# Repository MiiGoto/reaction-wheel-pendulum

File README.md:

# reaction-wheel-pendulum

最新方針（2026-10-08）: [1軸を保持して3軸へ発展する案B](docs/design_direction.md)を暫定第一候補にしました。指定X機体の同一性は未確認。GB54直結の自力起き上がりは仮定付き角運動量screeningで不適合。新しい[Inventor配置概念/STEP](mechanical/cubli_concept/README.md)と固定支点simulationを追加しましたが、製作可能な機構・実機性能・起き上がりは未完成です。[検証計画](docs/validation_plan.md)を参照してください。既存1軸native設計と未コミット変更は元checkoutに保持。

以下は既存1軸PCBの基準。機構・motor・driverの採用確定を意味しません。

1自由度リアクションホイール型倒立振子を製作し、制御モデルと実機の対応を検証する開発プロジェクトです。回路、STM32ファームウェア、シミュレーション、機構、試験記録を一つのGit repositoryで管理します。

## Project overview / System concept

BLDCでホイールを加減速し、その反作用で振子の姿勢を制御します。IMU、振子角度、ホイール角度・速度を取得し、PCでログを収集します。寸法目安は振子長約220 mm、ホイール径約130 mm、ホイール質量候補約90 gです。重心・慣性・最大速度・必要トルクは未決です。

## Hardware

制御基板MCUはSTM32G431RBT6（LQFP64、128 KB Flash / 32 KB RAM）を採用。NucleoとB-G431B-ESC1を評価候補とし、初期試作では外部ESCを優先します。Task 2では安定化5 V入力、AP2112K-3.3 LDO、MCU基本回路とSWDを実装。Task 3ではTCAN3413DR CAN FD、LSM6DSLTR SPI、外付け3.3 V ABI Encoder、外部ESC PWM/ENABLE/FAULT、UART接続を追加。Encoder/ESCの型番、最高RPM、モータ電源は未決です。

KiCad 10.0.6で `hardware/kicad/reaction_wheel_controller.kicad_pro` を開きます。rootは概念ブロックの概要、階層sheetはMCU/電源/SWD、CAN/IMU、Encoder/ESC、UARTに分割した実回路です。Task 4で90×70 mm・4層・4点M3固定穴の暫定PCB配置を追加しました。Task 5で全ネットの配線とprototype範囲のPCBレビューを完了しました。DRC Error0／Warning0／未配線0。製造承認・実機検証は未実施です。ERCの合格は実回路の正しさを意味しません。

## Firmware

`firmware/stm32/` は評価方針と要件を保管します。ターゲット・ESC通信方式の決定後にCubeMX/CubeIDEプロジェクトを作成します。まだ実行可能なファームウェアはありません。

## Simulation

`simulation/` はモデル仕様の初期整理です。実測または根拠のあるパラメータを登録した後、非線形モデル、線形化、PID、状態フィードバック、LQR、swing-up、推定、同定、sim2realへ進みます。現時点で制御性能は検証されていません。

## Repository structure

```text
hardware/kicad/   KiCad project, concept overview, MCU/power/SWD and interface schematics
firmware/stm32/   Firmware scope and future STM32 project
simulation/      Model and parameter requirements
mechanical/      Geometry, inertia and fixture requirements
docs/            Architecture, pin needs, power, bring-up, evidence
test/            Verification plan
```

最初に [PROJECT_CONTEXT.md](PROJECT_CONTEXT.md)、[requirements.md](requirements.md)、[AGENTS.md](AGENTS.md) を読んでください。環境調査は [docs/environment.md](docs/environment.md)、資料確認状態は [docs/sources.md](docs/sources.md) に記録します。

## Current status

Task5の配線・prototype範囲のレビューを完了しました。KiCad10.0.6のDRC Error0／Warning0／未配線0／回路図等価性問題0、ERC Error0／意図的Warning1。90×70mm・4層、548配線segment・155via、全部品配置と電気pin assignmentを保持しています。

[最新routing review](docs/task5_routing_review.md)、[current checkpoint](docs/task5_routing_checkpoint.md)、[検証記録](docs/validation.md)。実際のESC／Encoder、最終BOM・製造stackup・実装・安全性・熱・EMIの確認は未完了です。製造データ・注文・firmware・通電試験・Task6は未実施です。

## Roadmap

1. 機構パラメータ、電源、BLDC、双方向トルクを扱えるESCと制御指令仕様を確定。
2. 評価ボードでセンサ取得、安全停止、PC logging、モータ単体評価。
3. 必要I/Oを確定し、MCU型番・packageと物理ピン番号を公式資料・CubeMXで照合。
4. 電源・MCU・デバッグの回路を段階的に作成し、毎回ERCを実行。
5. CAN・センサ・ESC接続を追加し、要求追跡とレビューを実施。
6. シミュレーションと同定により制御を検証し、安全治具で実機評価。
7. 回路承認後にPCB設計・DRC・製造レビューへ進む。

## Publication and license

公開ファイルは本プロジェクト用の文書・設計です。回路図内のKiCad標準symbolは[ライブラリの設計成果物例外](https://www.kicad.org/libraries/license/)を確認済みです。ベンダーのPDF、SDK、HAL、独立した第三者ライブラリ集、ツールの実行ファイルは含めません。プロジェクトのライセンス選択はTBDです。公開されていること自体は第三者コードの利用許諾を意味しません。

## Detailed Cubli Rev A status (2026-10-08)

Detailed fabrication CAD has **not** been completed. The three-axis clearance
study is preserved. A new motor/brake/contact gate identifies insufficient GB54
momentum and an unsafe direct cantilever brake-loaded motor shaft. Three named
motor alternatives and three size options are compared in
[the Rev A gate report](docs/cubli_reva_design_gate.md). No new manufacturing
files or physical actions are released. Requested detailed CAD remains blocked
pending a qualified actuator/brake/support/power module.

## Current one-wheel native CAD milestone

Inventor2026.2で36部品・104拘束の1輪モジュールを作成、保存後に再読込しました。7姿勢のネイティブ干渉検査は0件。STEP37件／STL3件／保留付き図面14件を生成。ブレーキアクチュエータ・継手・保持公差・強度と3軸起き上がりは未検証です。製造承認済みではありません。詳細は[検証報告](docs/one_wheel_module_review.md)と[モジュール成果](mechanical/cubli_reva/one_wheel_module/README.md)を参照してください。

Rev B: actual lightened Inventor one-wheel module and orthogonal three-axis packing study.
See [review](docs/cubli_revb_review.md) and [manufacturing holds](docs/manufacturing_holds.md).
Self-righting, high-speed safety and fabrication remain unqualified. Native CAD is local; own STEP/PDF/scripts published.

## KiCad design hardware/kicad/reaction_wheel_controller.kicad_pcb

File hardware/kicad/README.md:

# reaction_wheel_controller

KiCad10.0.6でreaction_wheel_controller.kicad_proを開く。rootは概念概要、階層sheetはMCU/電源/SWD、CAN/IMU、Encoder/ESC、UARTの実回路。Task5でreaction_wheel_controller.kicad_pcbの全ネット配線を完了。90x70mm、4層、86footprints、548segments、155via、R0.5。

NativeDRC0Errors/0Warnings/0unrouted/0parity、ERC0Errors/1intentionalSDX/GNDWarning。主要設計ファイルとproject-local symbol table、custom design rulesを追跡。outputs/はlocal report・preview・checkpoint用でignored。VendorPDF/tools/SDK、Gerber/drill/PnPは公開せず、製造出力自体未実施。

DRC合格は製造承認・実機適合ではない。ExactBOM/stackup/assembly/encoder/ESC/mechanical/safety/thermal/EMIは未検証。[routing review](../../docs/task5_routing_review.md)、[validation](../../docs/validation.md)、[bring-up](../../docs/bringup.md)参照。未使用/予約MCUpinは意図的NC、firmware未実装。

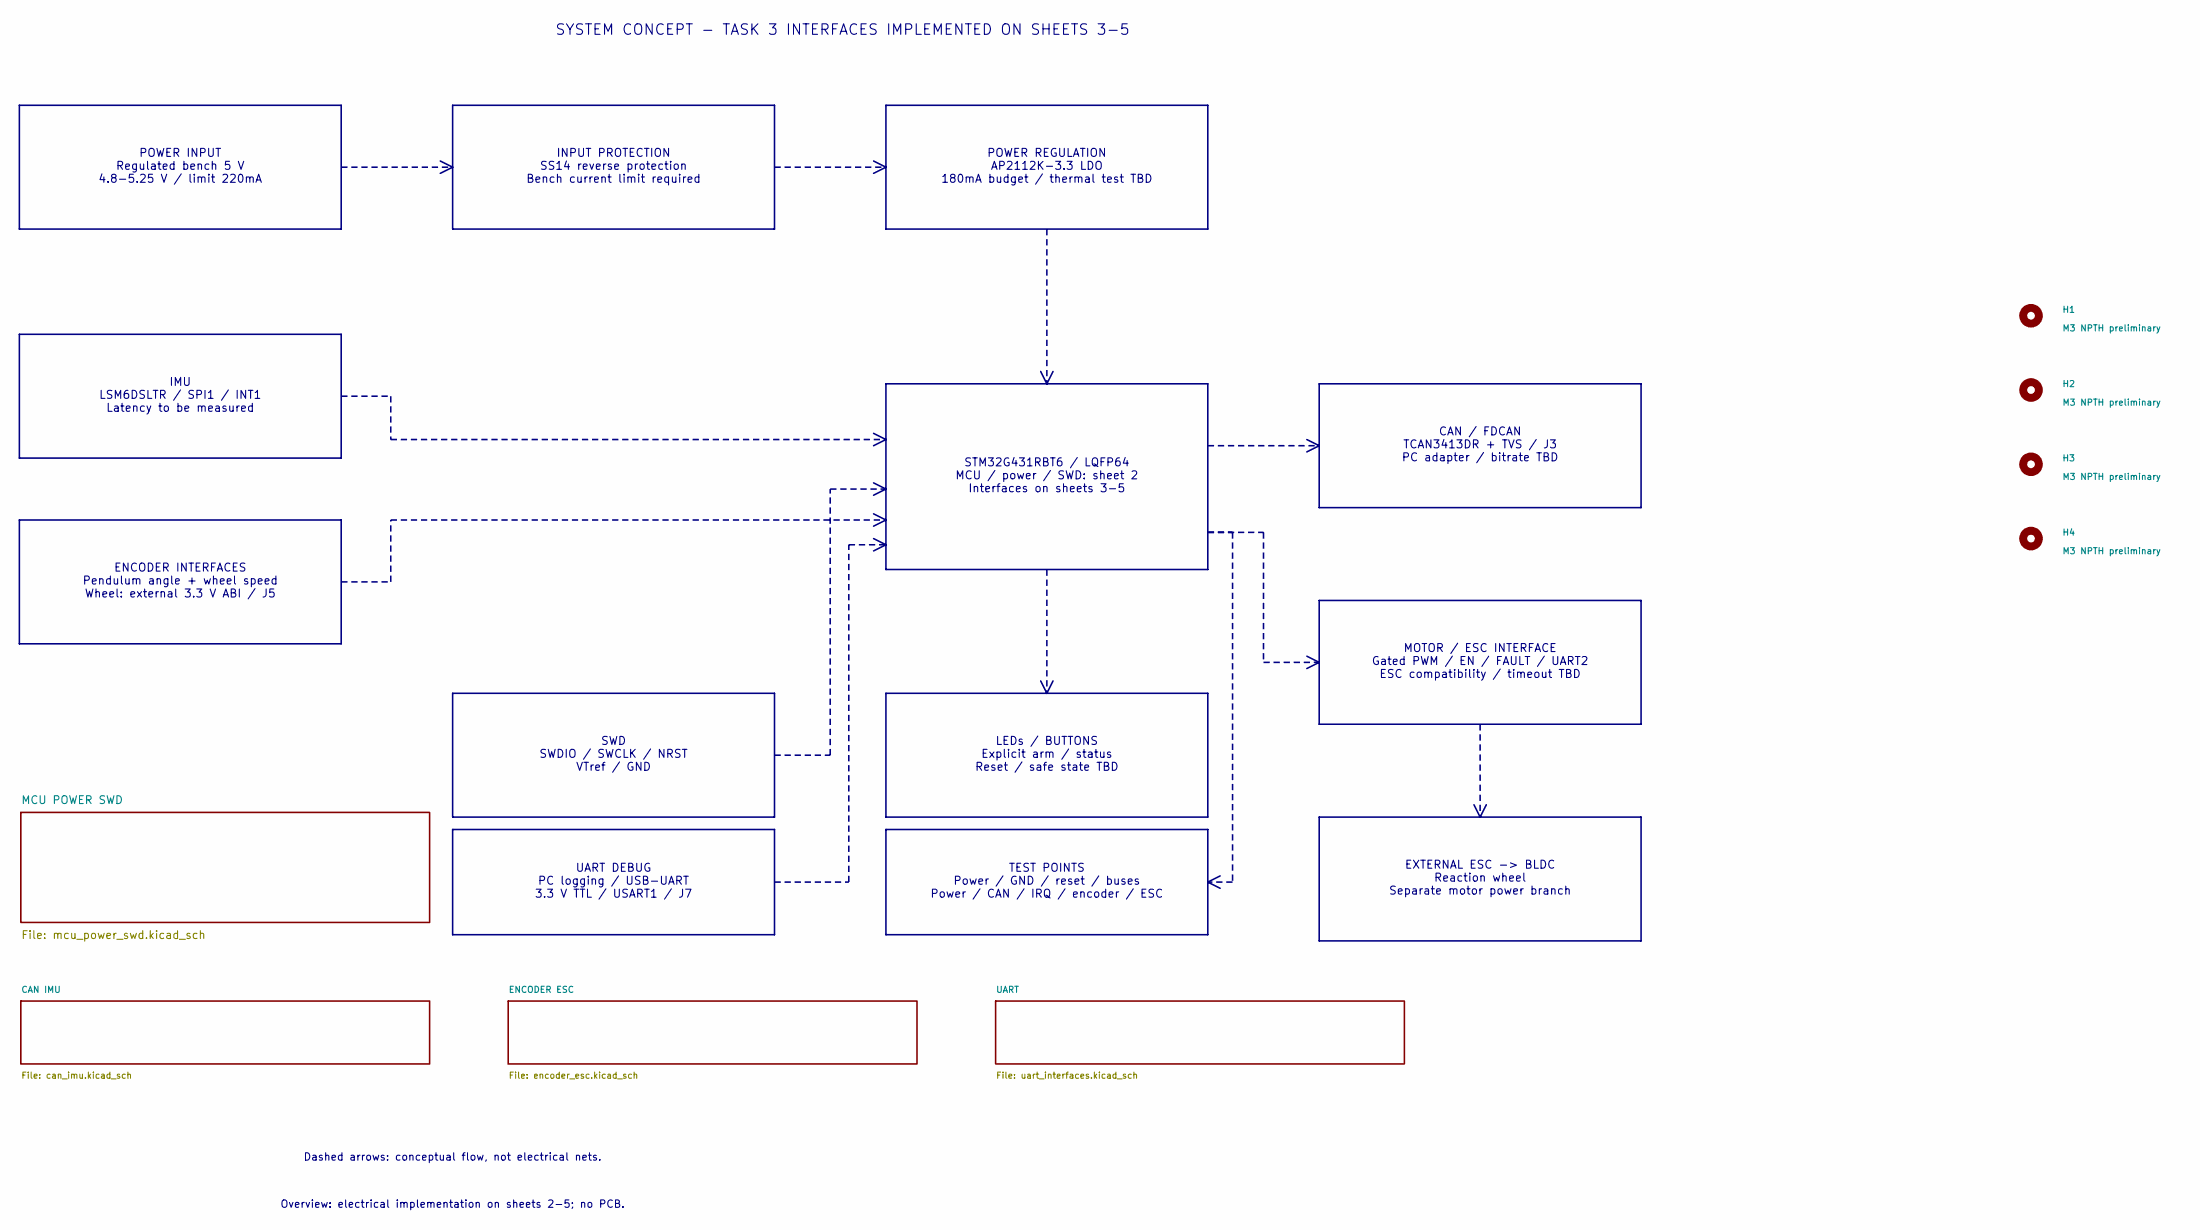
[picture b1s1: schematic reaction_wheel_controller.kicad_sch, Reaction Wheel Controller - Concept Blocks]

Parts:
H1, H2, H3, H4: M3 NPTH preliminary; MountingHole_3.2mm_M3

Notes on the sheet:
SYSTEM CONCEPT - TASK 3 INTERFACES IMPLEMENTED ON SHEETS 3-5
POWER INPUT Regulated bench 5 V 4.8-5.25 V / limit 220mA
INPUT PROTECTION SS14 reverse protection Bench current limit required
POWER REGULATION AP2112K-3.3 LDO 180mA budget / thermal test TBD
STM32G431RBT6 / LQFP64 MCU / power / SWD: sheet 2 Interfaces on sheets 3-5
IMU LSM6DSLTR / SPI1 / INT1 Latency to be measured
ENCODER INTERFACES Pendulum angle + wheel speed Wheel: external 3.3 V ABI / J5
CAN / FDCAN TCAN3413DR + TVS / J3 PC adapter / bitrate TBD
MOTOR / ESC INTERFACE Gated PWM / EN / FAULT / UART2 ESC compatibility / timeout TBD
EXTERNAL ESC -> BLDC Reaction wheel Separate motor power branch
SWD SWDIO / SWCLK / NRST VTref / GND
UART DEBUG PC logging / USB-UART 3.3 V TTL / USART1 / J7
LEDs / BUTTONS Explicit arm / status Reset / safe state TBD
TEST POINTS Power / GND / reset / buses Power / CAN / IRQ / encoder / ESC
Dashed arrows: conceptual flow, not electrical nets.
Overview: electrical implementation on sheets 2-5; no PCB.

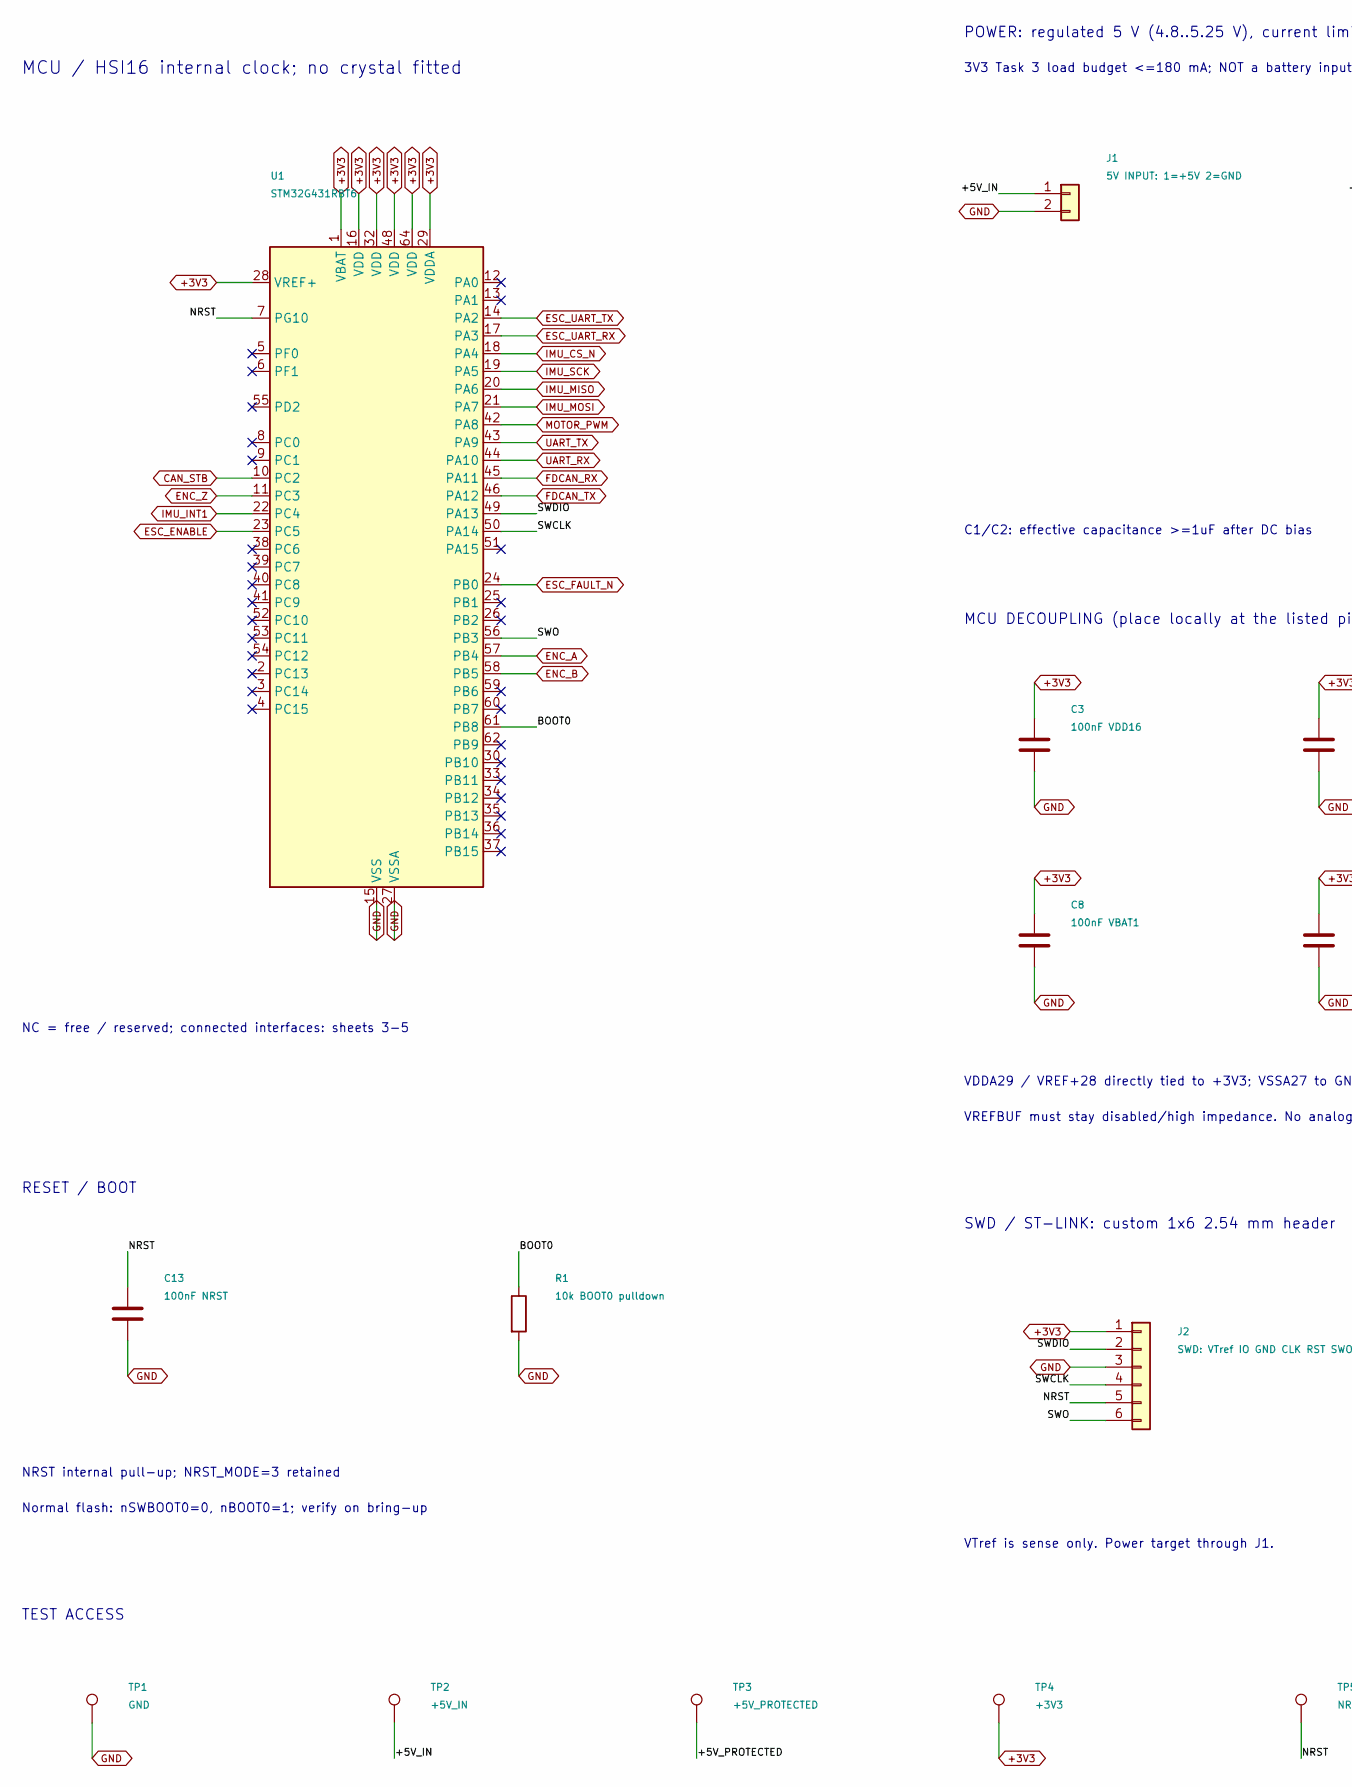
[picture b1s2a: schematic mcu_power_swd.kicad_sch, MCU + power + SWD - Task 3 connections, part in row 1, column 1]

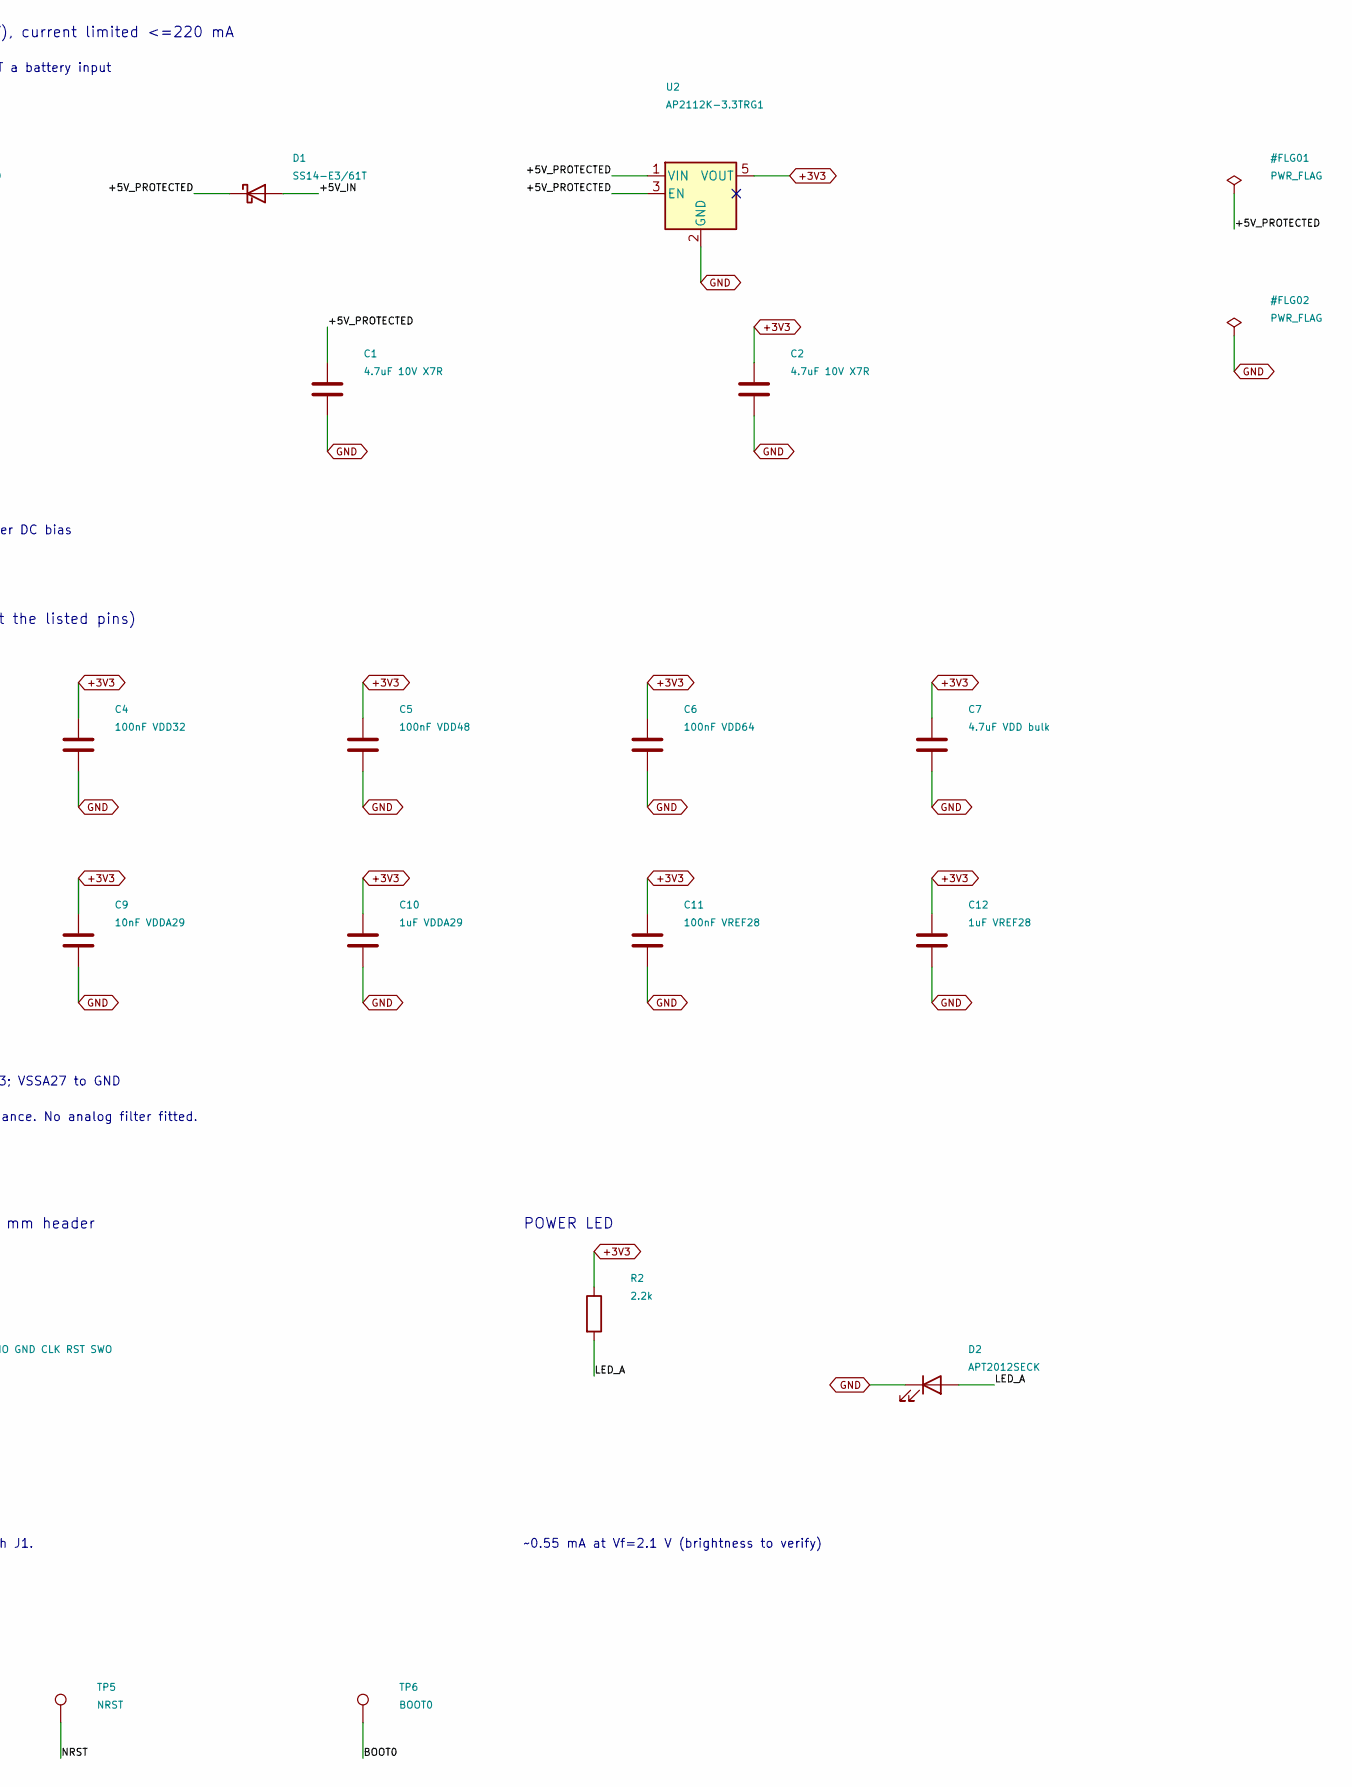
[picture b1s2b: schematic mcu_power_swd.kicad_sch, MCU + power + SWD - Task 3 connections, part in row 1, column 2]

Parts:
C1, C2: 4.7uF 10V X7R; C_0805_2012Metric
C3: 100nF VDD16; C_0805_2012Metric
C4: 100nF VDD32; C_0805_2012Metric
C5: 100nF VDD48; C_0805_2012Metric
C6: 100nF VDD64; C_0805_2012Metric
C7: 4.7uF VDD bulk; C_0805_2012Metric
C8: 100nF VBAT1; C_0805_2012Metric
C9: 10nF VDDA29; C_0805_2012Metric
C10: 1uF VDDA29; C_0805_2012Metric
C11: 100nF VREF28; C_0805_2012Metric
C12: 1uF VREF28; C_0805_2012Metric
C13: 100nF NRST; C_0805_2012Metric
D1: SS14-E3/61T; D_SMA
D2: APT2012SECK; LED_0805_2012Metric
J1: 5V INPUT: 1=+5V 2=GND; PinHeader_1x02_P2.54mm_Vertical
J2: SWD: VTref IO GND CLK RST SWO; PinHeader_1x06_P2.54mm_Vertical
R1: 10k BOOT0 pulldown; R_0805_2012Metric
R2: 2.2k; R_0805_2012Metric
TP1: GND; TestPoint_Pad_D1.5mm
TP2: +5V_IN; TestPoint_Pad_D1.5mm
TP3: +5V_PROTECTED; TestPoint_Pad_D1.5mm
TP4: +3V3; TestPoint_Pad_D1.5mm
TP5: NRST; TestPoint_Pad_D1.5mm
TP6: BOOT0; TestPoint_Pad_D1.5mm
U1: STM32G431RBT6; LQFP-64_10x10mm_P0.5mm
U2: AP2112K-3.3TRG1; SOT-23-5

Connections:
+3V3: C2.1, C3.1, C4.1, C5.1, C6.1, C7.1, C8.1, C9.1, C10.1, C11.1, C12.1, J2.1, R2.1, TP4.1, U1.1 (VBAT), U1.16 (VDD), U1.28 (VREF+), U1.29 (VDDA), U1.32 (VDD), U1.48 (VDD), U1.64 (VDD), U2.5 (VOUT); also elsewhere on the board
/MCU POWER SWD/+5V_IN: D1.2 (A), J1.1, TP2.1
/MCU POWER SWD/+5V_PROTECTED: C1.1, D1.1 (K), TP3.1, U2.1 (VIN), U2.3 (EN)
/MCU POWER SWD/BOOT0: R1.1, TP6.1, U1.61 (PB8)
/MCU POWER SWD/LED_A: D2.2 (A), R2.2
/MCU POWER SWD/NRST: C13.1, J2.5, TP5.1, U1.7 (PG10)
/MCU POWER SWD/SWCLK: J2.4, U1.50 (PA14)
/MCU POWER SWD/SWDIO: J2.2, U1.49 (PA13)
/MCU POWER SWD/SWO: J2.6, U1.56 (PB3)
CAN_STB: U1.10 (PC2); also elsewhere on the board
ENC_A: U1.57 (PB4); also elsewhere on the board
ENC_B: U1.58 (PB5); also elsewhere on the board
ENC_Z: U1.11 (PC3); also elsewhere on the board
ESC_ENABLE: U1.23 (PC5); also elsewhere on the board
ESC_FAULT_N: U1.24 (PB0); also elsewhere on the board
ESC_UART_RX: U1.17 (PA3); also elsewhere on the board
ESC_UART_TX: U1.14 (PA2); also elsewhere on the board
FDCAN_RX: U1.45 (PA11); also elsewhere on the board
FDCAN_TX: U1.46 (PA12); also elsewhere on the board
GND: C1.2, C2.2, C3.2, C4.2, C5.2, C6.2, C7.2, C8.2, C9.2, C10.2, C11.2, C12.2, C13.2, D2.1 (K), J1.2, J2.3, R1.2, TP1.1, U1.15 (VSS), U1.27 (VSSA), U1.31 (VSS), U1.47 (VSS), U1.63 (VSS), U2.2 (GND); also elsewhere on the board
IMU_CS_N: U1.18 (PA4); also elsewhere on the board
IMU_INT1: U1.22 (PC4); also elsewhere on the board
IMU_MISO: U1.20 (PA6); also elsewhere on the board
IMU_MOSI: U1.21 (PA7); also elsewhere on the board
IMU_SCK: U1.19 (PA5); also elsewhere on the board
MOTOR_PWM: U1.42 (PA8); also elsewhere on the board
UART_RX: U1.44 (PA10); also elsewhere on the board
UART_TX: U1.43 (PA9); also elsewhere on the board

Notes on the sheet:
MCU / HSI16 internal clock; no crystal fitted
NC = free / reserved; connected interfaces: sheets 3-5
POWER: regulated 5 V (4.8..5.25 V), current limited <=220 mA
3V3 Task 3 load budget <=180 mA; NOT a battery input
C1/C2: effective capacitance >=1uF after DC bias
MCU DECOUPLING (place locally at the listed pins)
VDDA29 / VREF+28 directly tied to +3V3; VSSA27 to GND
VREFBUF must stay disabled/high impedance. No analog filter fitted.
RESET / BOOT
NRST internal pull-up; NRST_MODE=3 retained
Normal flash: nSWBOOT0=0, nBOOT0=1; verify on bring-up
SWD / ST-LINK: custom 1x6 2.54 mm header
VTref is sense only. Power target through J1.
POWER LED
~0.55 mA at Vf=2.1 V (brightness to verify)
TEST ACCESS

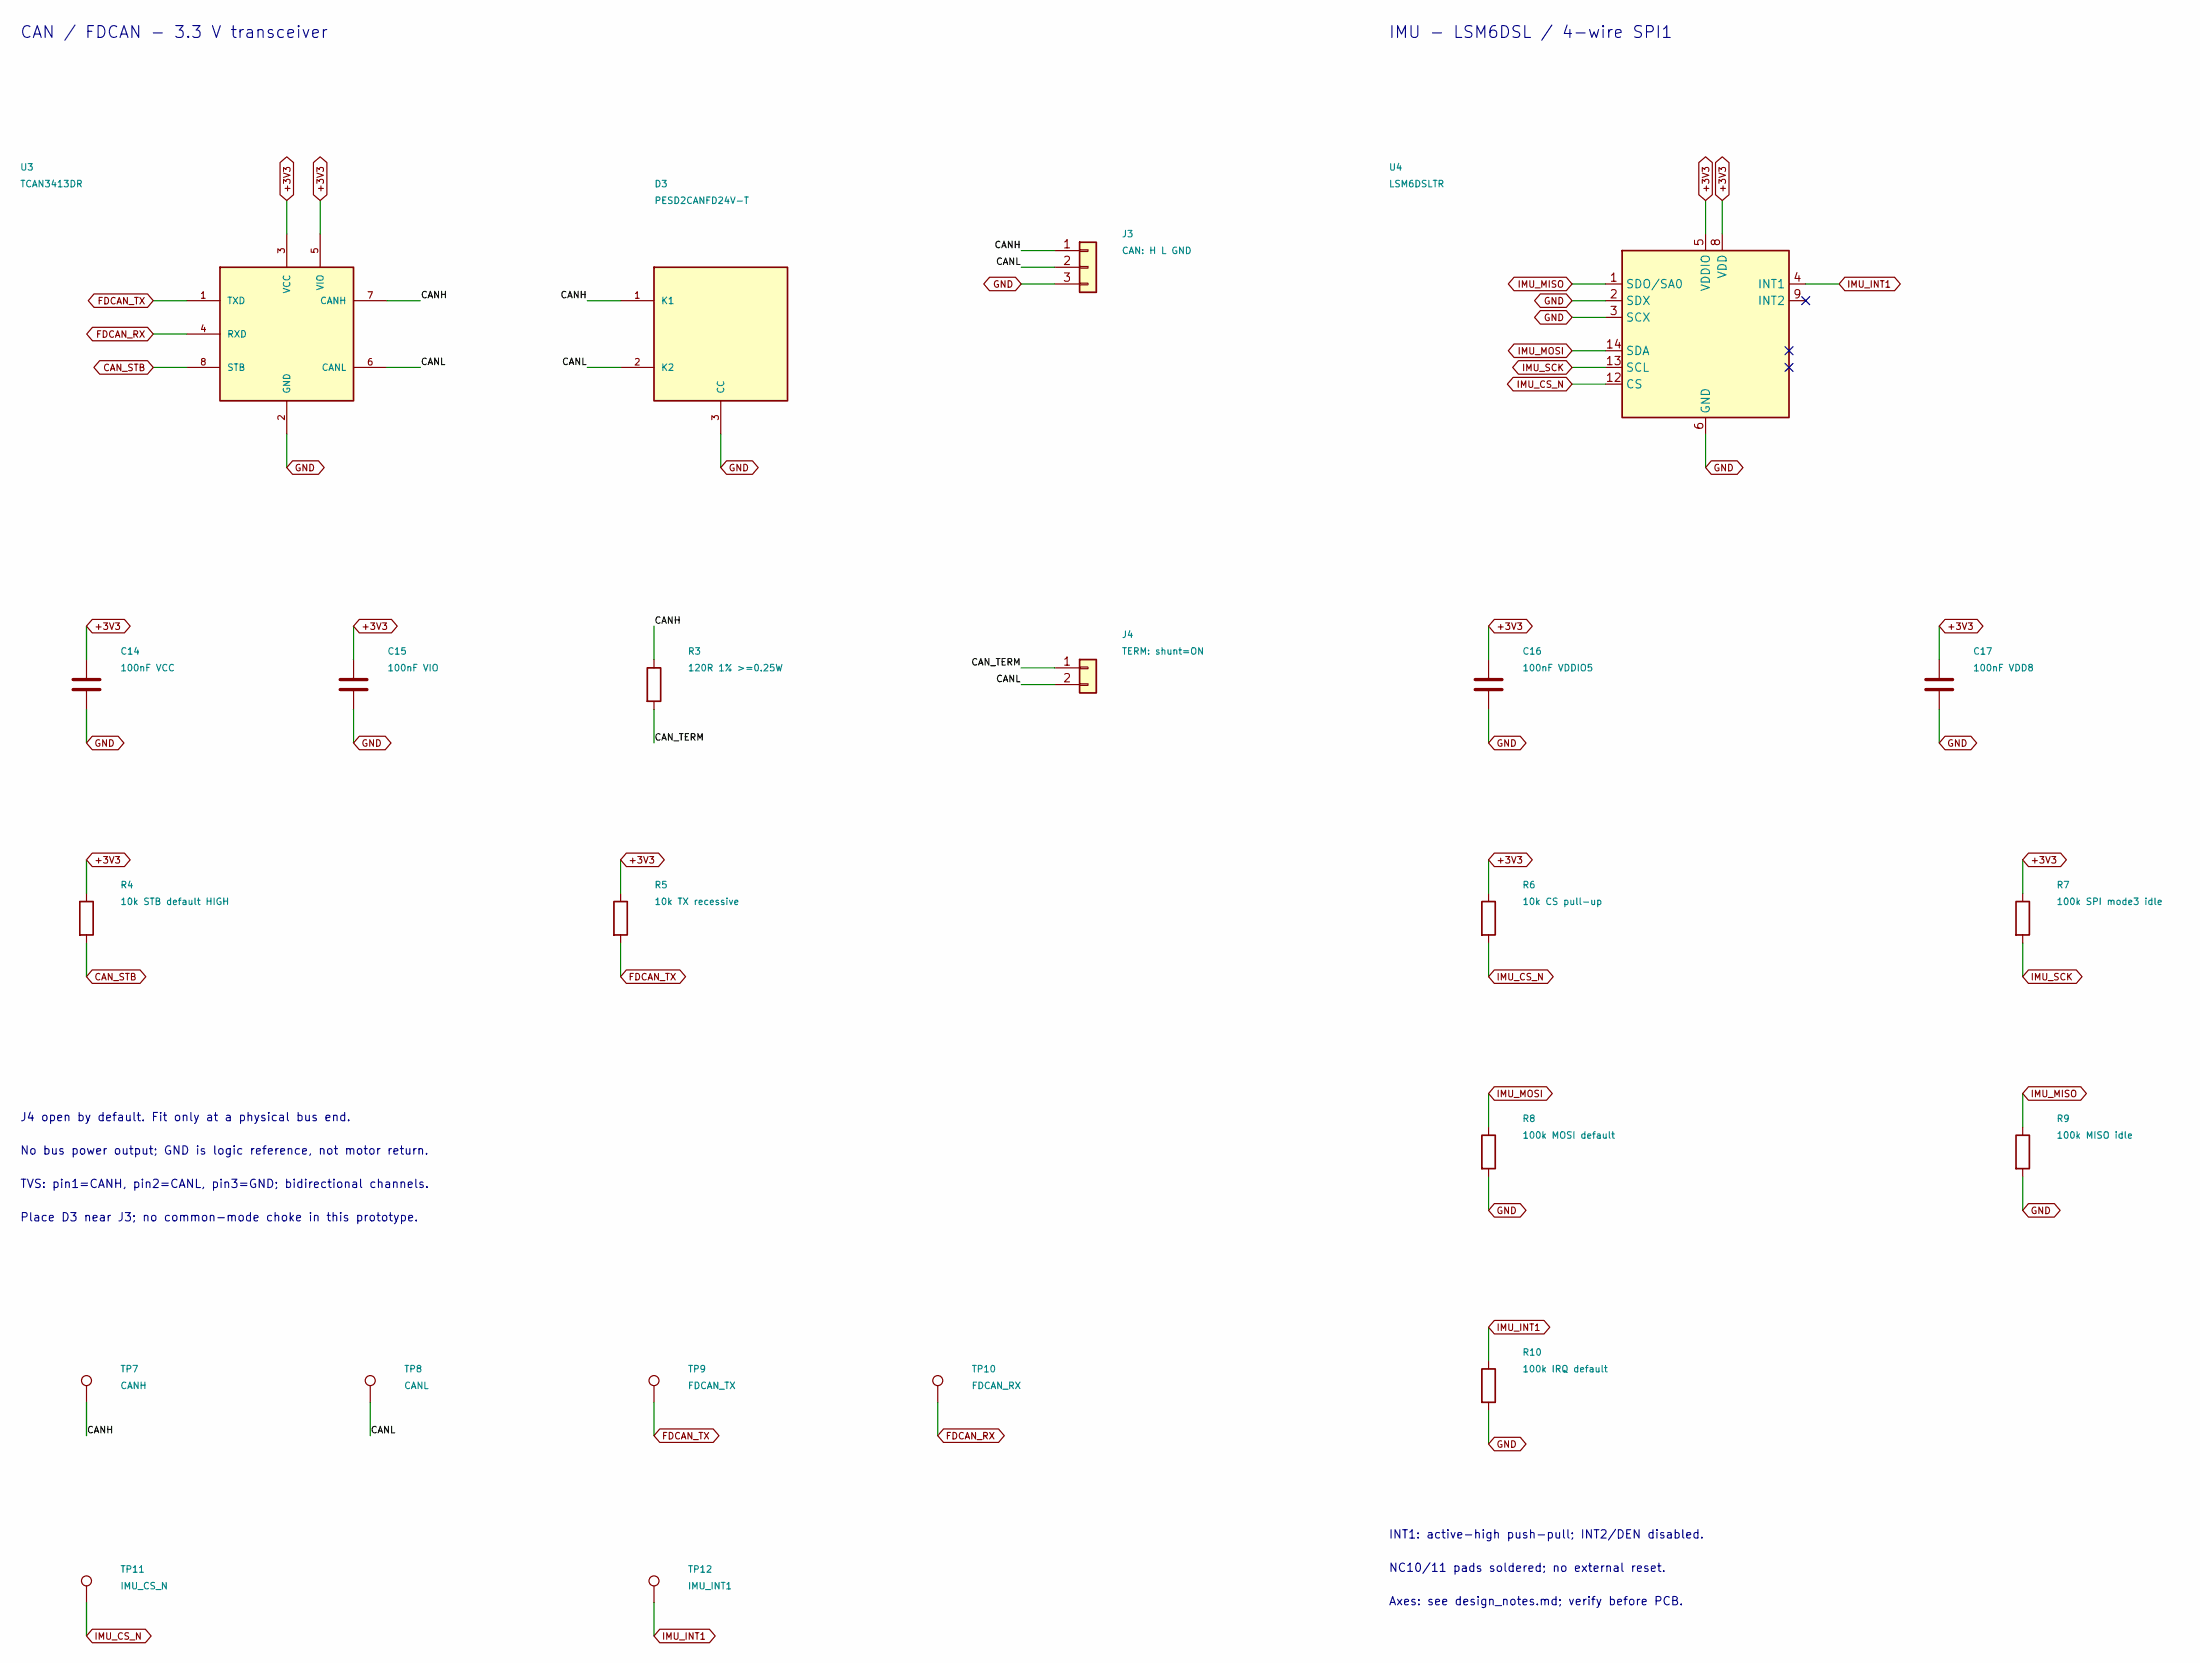
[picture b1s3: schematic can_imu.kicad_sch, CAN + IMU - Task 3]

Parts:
C14: 100nF VCC; C_0805_2012Metric
C15: 100nF VIO; C_0805_2012Metric
C16: 100nF VDDIO5; C_0805_2012Metric
C17: 100nF VDD8; C_0805_2012Metric
D3: PESD2CANFD24V-T; SOT-23
J3: CAN: H L GND; PinHeader_1x03_P2.54mm_Vertical
J4: TERM: shunt=ON; PinHeader_1x02_P2.54mm_Vertical
R3: 120R 1% >=0.25W; R_1206_3216Metric
R4: 10k STB default HIGH; R_0805_2012Metric
R5: 10k TX recessive; R_0805_2012Metric
R6: 10k CS pull-up; R_0805_2012Metric
R7: 100k SPI mode3 idle; R_0805_2012Metric
R8: 100k MOSI default; R_0805_2012Metric
R9: 100k MISO idle; R_0805_2012Metric
R10: 100k IRQ default; R_0805_2012Metric
TP7: CANH; TestPoint_Pad_D1.5mm
TP8: CANL; TestPoint_Pad_D1.5mm
TP9: FDCAN_TX; TestPoint_Pad_D1.5mm
TP10: FDCAN_RX; TestPoint_Pad_D1.5mm
TP11: IMU_CS_N; TestPoint_Pad_D1.5mm
TP12: IMU_INT1; TestPoint_Pad_D1.5mm
U3: TCAN3413DR; SOIC-8_3.9x4.9mm_P1.27mm
U4: LSM6DSLTR; LGA-14_3x2.5mm_P0.5mm_LayoutBorder3x4y

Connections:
+3V3: C14.1, C15.1, C16.1, C17.1, R4.1, R5.1, R6.1, R7.1, U3.3 (VCC), U3.5 (VIO), U4.5 (VDDIO), U4.8 (VDD); also elsewhere on the board
/CAN IMU/CANH: D3.1 (K1), J3.1, R3.1, TP7.1, U3.7 (CANH)
/CAN IMU/CANL: D3.2 (K2), J3.2, J4.2, TP8.1, U3.6 (CANL)
/CAN IMU/CAN_TERM: J4.1, R3.2
CAN_STB: R4.2, U3.8 (STB); also elsewhere on the board
FDCAN_RX: TP10.1, U3.4 (RXD); also elsewhere on the board
FDCAN_TX: R5.2, TP9.1, U3.1 (TXD); also elsewhere on the board
GND: C14.2, C15.2, C16.2, C17.2, D3.3 (CC), J3.3, R8.2, R9.2, R10.2, U3.2 (GND), U4.2 (SDX), U4.3 (SCX), U4.6 (GND), U4.7 (GND); also elsewhere on the board
IMU_CS_N: R6.2, TP11.1, U4.12 (CS); also elsewhere on the board
IMU_INT1: R10.1, TP12.1, U4.4 (INT1); also elsewhere on the board
IMU_MISO: R9.1, U4.1 (SDO/SA0); also elsewhere on the board
IMU_MOSI: R8.1, U4.14 (SDA); also elsewhere on the board
IMU_SCK: R7.2, U4.13 (SCL); also elsewhere on the board

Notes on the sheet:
CAN / FDCAN - 3.3 V transceiver
J4 open by default. Fit only at a physical bus end.
No bus power output; GND is logic reference, not motor return.
TVS: pin1=CANH, pin2=CANL, pin3=GND; bidirectional channels.
Place D3 near J3; no common-mode choke in this prototype.
IMU - LSM6DSL / 4-wire SPI1
INT1: active-high push-pull; INT2/DEN disabled.
NC10/11 pads soldered; no external reset.
Axes: see design_notes.md; verify before PCB.

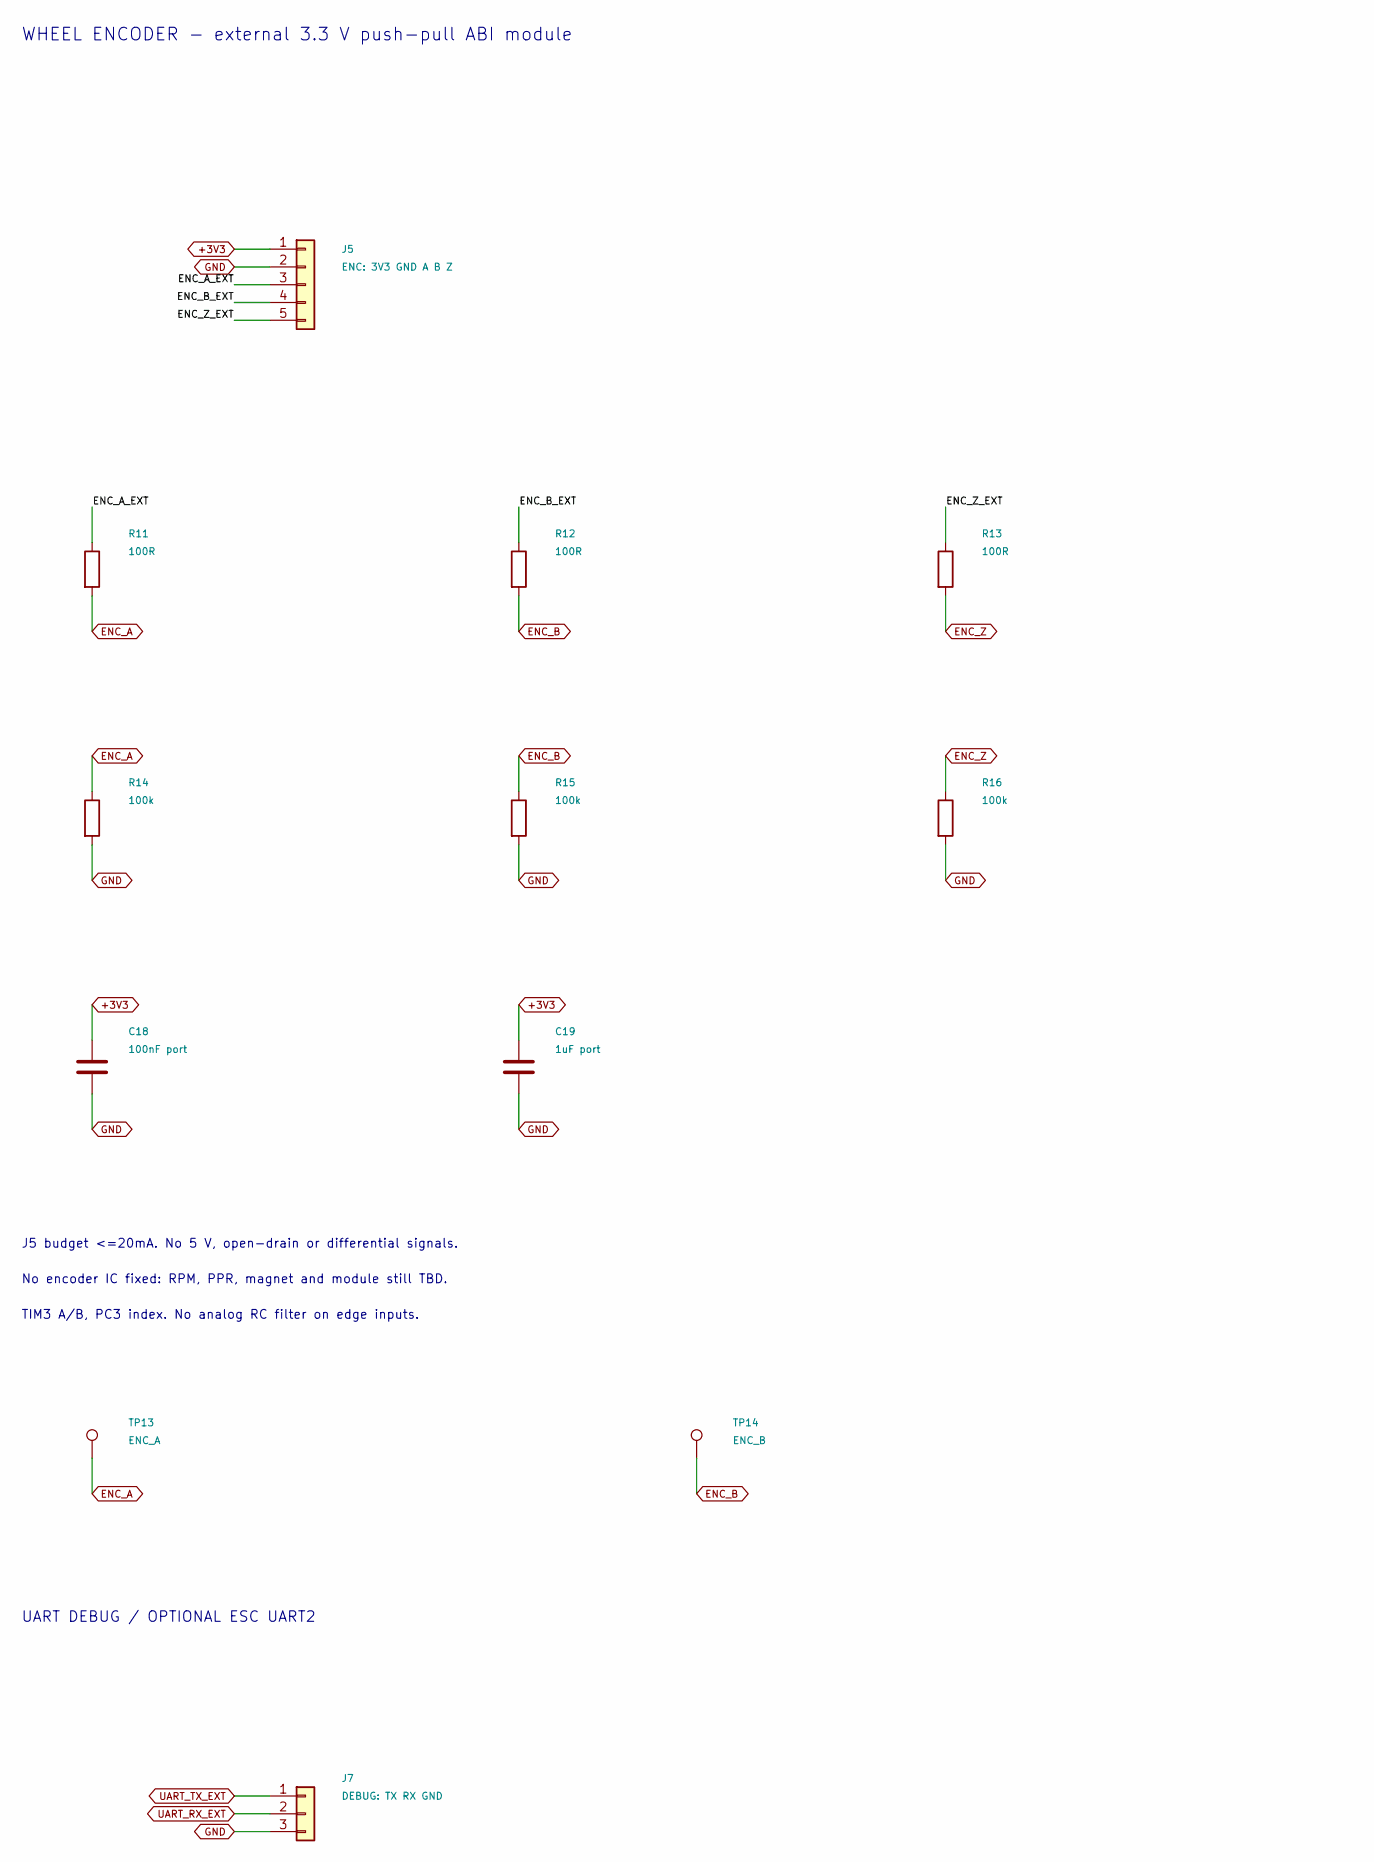
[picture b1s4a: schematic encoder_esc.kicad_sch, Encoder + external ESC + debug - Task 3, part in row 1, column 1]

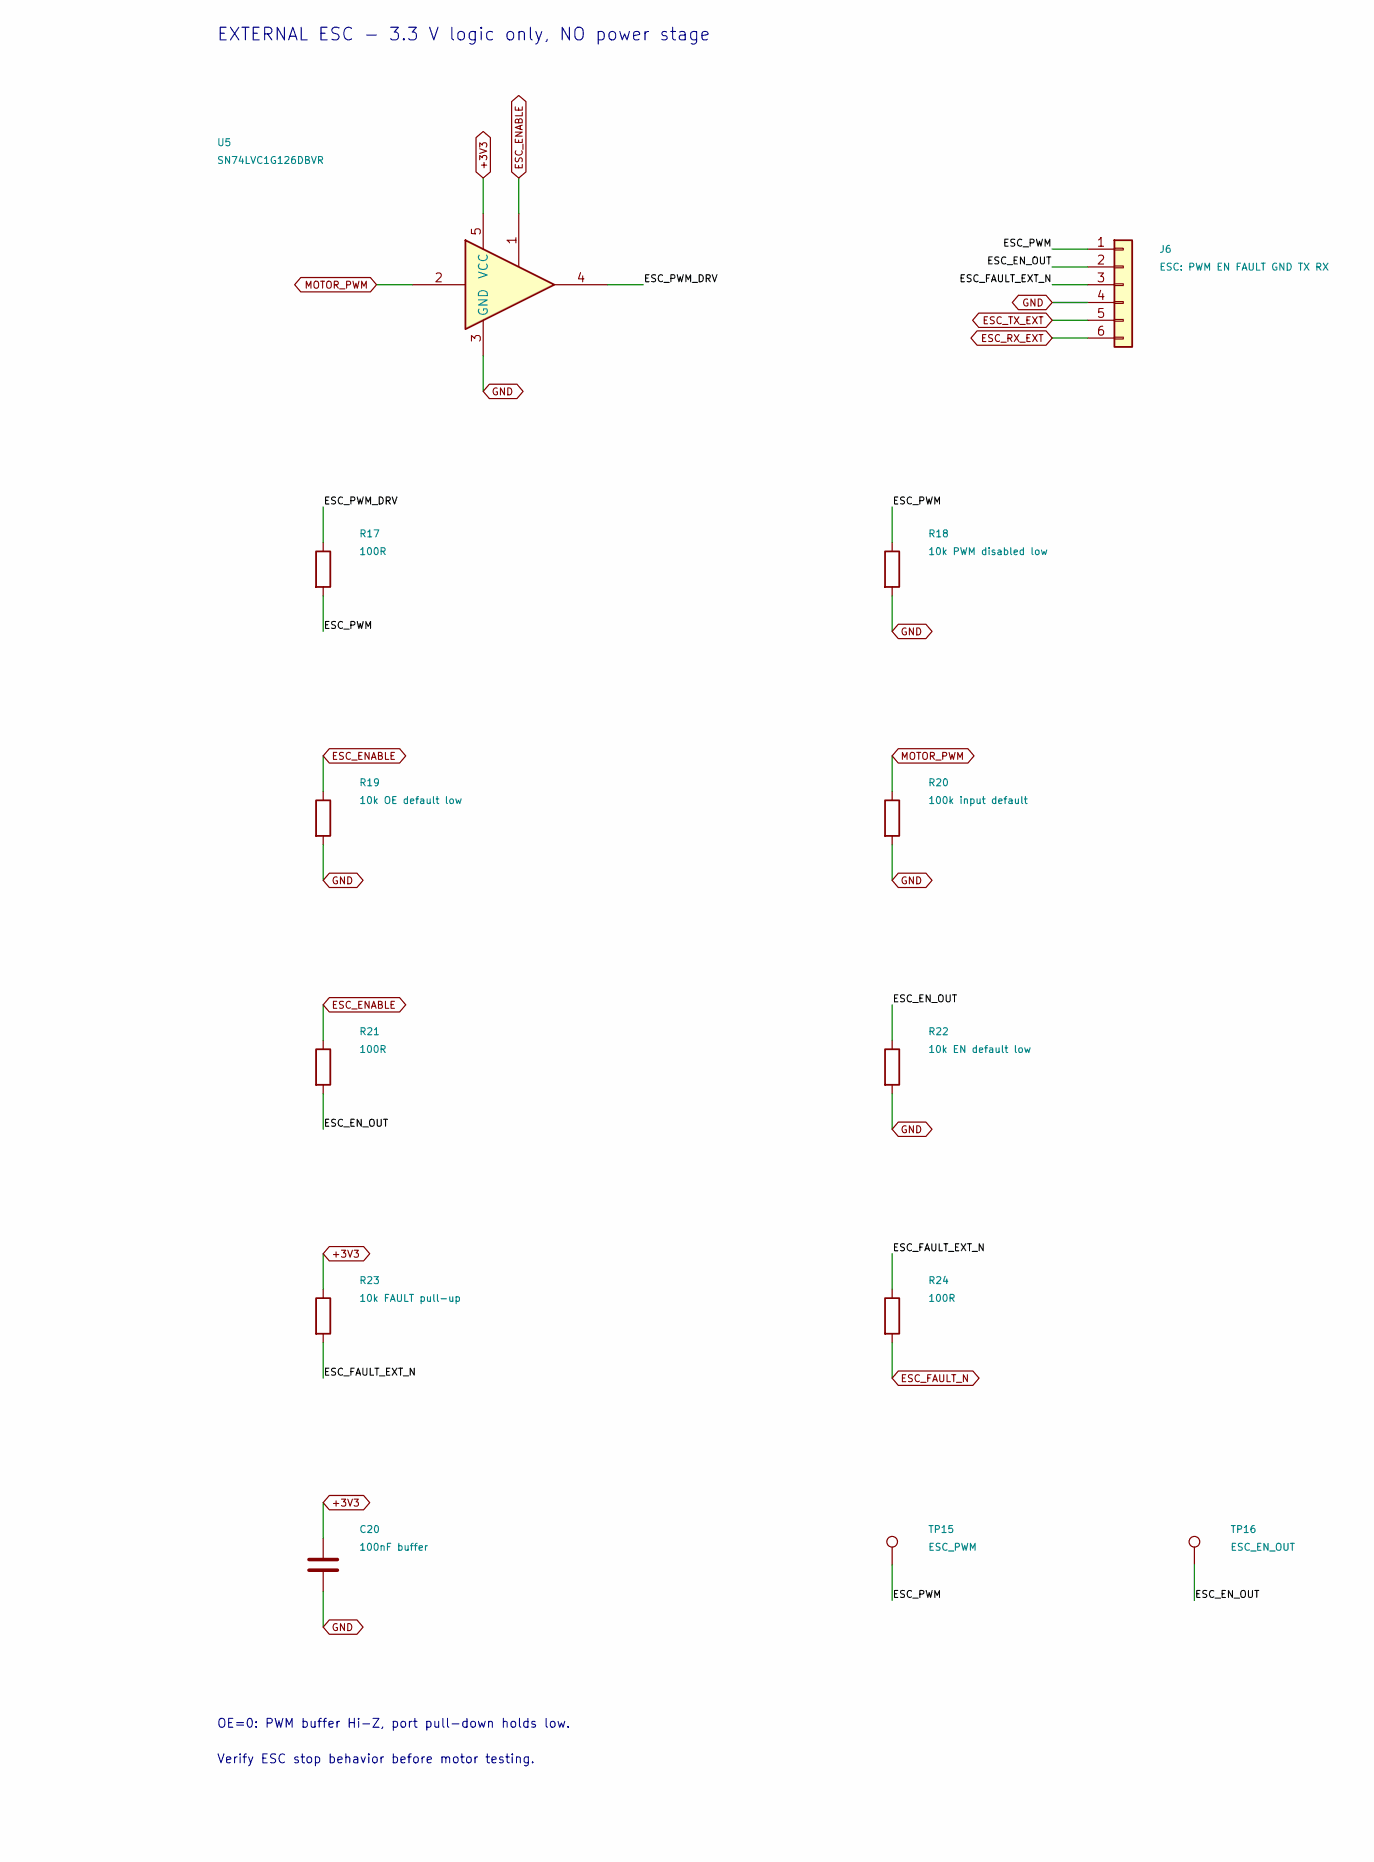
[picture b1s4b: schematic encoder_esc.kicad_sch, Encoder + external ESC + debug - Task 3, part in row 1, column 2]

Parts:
C18: 100nF port; C_0805_2012Metric
C19: 1uF port; C_0805_2012Metric
C20: 100nF buffer; C_0805_2012Metric
J5: ENC: 3V3 GND A B Z; PinHeader_1x05_P2.54mm_Vertical
J6: ESC: PWM EN FAULT GND TX RX; PinHeader_1x06_P2.54mm_Vertical
J7: DEBUG: TX RX GND; PinHeader_1x03_P2.54mm_Vertical
R11, R12, R13, R17, R21, R24: 100R; R_0805_2012Metric
R14, R15, R16: 100k; R_0805_2012Metric
R18: 10k PWM disabled low; R_0805_2012Metric
R19: 10k OE default low; R_0805_2012Metric
R20: 100k input default; R_0805_2012Metric
R22: 10k EN default low; R_0805_2012Metric
R23: 10k FAULT pull-up; R_0805_2012Metric
TP13: ENC_A; TestPoint_Pad_D1.5mm
TP14: ENC_B; TestPoint_Pad_D1.5mm
TP15: ESC_PWM; TestPoint_Pad_D1.5mm
TP16: ESC_EN_OUT; TestPoint_Pad_D1.5mm
U5: SN74LVC1G126DBVR; SOT-23-5

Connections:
+3V3: C18.1, C19.1, C20.1, J5.1, R23.1, U5.5 (VCC); also elsewhere on the board
/ENCODER ESC/ENC_A_EXT: J5.3, R11.1
/ENCODER ESC/ENC_B_EXT: J5.4, R12.1
/ENCODER ESC/ENC_Z_EXT: J5.5, R13.1
/ENCODER ESC/ESC_EN_OUT: J6.2, R21.2, R22.1, TP16.1
/ENCODER ESC/ESC_FAULT_EXT_N: J6.3, R23.2, R24.1
/ENCODER ESC/ESC_PWM: J6.1, R17.2, R18.1, TP15.1
/ENCODER ESC/ESC_PWM_DRV: R17.1, U5.4
ENC_A: R11.2, R14.1, TP13.1; also elsewhere on the board
ENC_B: R12.2, R15.1, TP14.1; also elsewhere on the board
ENC_Z: R13.2, R16.1; also elsewhere on the board
ESC_ENABLE: R19.1, R21.1, U5.1; also elsewhere on the board
ESC_FAULT_N: R24.2; also elsewhere on the board
ESC_RX_EXT: J6.6; also elsewhere on the board
ESC_TX_EXT: J6.5; also elsewhere on the board
GND: C18.2, C19.2, C20.2, J5.2, J6.4, J7.3, R14.2, R15.2, R16.2, R18.2, R19.2, R20.2, R22.2, U5.3 (GND); also elsewhere on the board
MOTOR_PWM: R20.1, U5.2; also elsewhere on the board
UART_RX_EXT: J7.2; also elsewhere on the board
UART_TX_EXT: J7.1; also elsewhere on the board

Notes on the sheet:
WHEEL ENCODER - external 3.3 V push-pull ABI module
J5 budget <=20mA. No 5 V, open-drain or differential signals.
No encoder IC fixed: RPM, PPR, magnet and module still TBD.
TIM3 A/B, PC3 index. No analog RC filter on edge inputs.
EXTERNAL ESC - 3.3 V logic only, NO power stage
OE=0: PWM buffer Hi-Z, port pull-down holds low.
Verify ESC stop behavior before motor testing.
UART DEBUG / OPTIONAL ESC UART2
